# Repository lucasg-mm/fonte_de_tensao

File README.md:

# Projeto 1 da Disciplina SCC0180: Fonte de Tensão

## Autor
Lucas Gabriel Mendes Miranda, 10265892

## Objetivo
Projetar uma fonte de tensão que forneça, na saída, uma tensão entre 3V e 12V com capacidade de 100mA.

## Diagrama da Fonte

## Lista de Componentes Utilizados

| Nome do Componente | Valor | Preço |
| --- | --- | --- |
| [Transformador](https://www.soldafria.com.br/componentes-eletronicos/transformador/2a/transformador-15v-2a-entrada-110-220vac) | 15V 2A | R$39,82 |
| [Diodo Zener BZX55C](https://www.baudaeletronica.com.br/diodo-zener-bzx55c-13v-0-5w.html) | 13V 0,5W | R$ 0,09 |
| [Resistor](https://www.baudaeletronica.com.br/resistor-1k8-5-1-4w.html) | 1,8k 5% (1/4W) | R$ 0,08 |
| [Resistor](https://www.baudaeletronica.com.br/resistor-1k8-1-2w.html) | 1k 5% (1/2W) | R$ 0,14 |
| [Resistor](https://www.baudaeletronica.com.br/resistor-2k2-5-1-4w.html) | 2,2k 5% (1/4W) | R$ 0,08 |
| [Potenciômetro Linear](https://www.baudaeletronica.com.br/potenciometro-linear-de-5k-5000.html) | 5k (0,2W) | R$ 1,09 |
| [Capacitor Eletrolítico](https://www.baudaeletronica.com.br/capacitor-eletrolitico-470uf-25v.html) | 470 uF / 25V | R$ 0,33 |
| 4 [Diodos 1N5404](https://www.baudaeletronica.com.br/diodo-1n5404.html) (para a ponte) | 3A | R$ 0,36 (cada)|
| [LED difuso 5mm vermelho](https://www.baudaeletronica.com.br/led-difuso-5mm-vermelho.html) | 2V 20mA | R$ 0,24 |
| [Transistor NPN BC337](https://www.baudaeletronica.com.br/transistor-npn-bc337.html) | VCEO = 45V, IC = 500mA | R$ 0,17 |

## Partes do Circuito e Justificativa dos Componentes

### Fonte de Tensão AC de 127V
A fonte foi projetada para funcionar com o fornecimento de uma tensão de 127V (RMS) em corrente alternada (AC). O simulador usado (Falstad) permite apenas definir a tensão máxima (peak) de uma fonte AC. Mas, sabemos que:

Então a tensão máxima dessa fonte foi ajustada para 179.6V no simulador. 

### Transformador
O transformador tem como objetivo diminuir o valor da tensão de 127V. Para determinar o valor do transformador necessário, foi preciso realizar alguns cálculos:

* Sabemos que a nossa fonte precisa fornecer no máximo **12V**

* Cada diodo tem uma queda de **0.7V**

* O circuito regulador precisa de aproximadamente **8.46V** para funcionar (quando a fonte fornece *12V*)

Somando os valores em negrito, temos uma tensão de pico de aproximadamente 21.16V, por isso, precisamos de um transformador de, no mínimo, 15V RMS, capaz de fornecer 500 mA.

### Ponte de Diodos (Rectifier)
A ponte de diodos converte a tensão AC do transformador numa tensão DC pulsante. 

### Capacitor (Filtro)
O capacitor diminui os pulsos da tensão fornecida pela ponte de diodos. O capacitor está submetido a uma tensão de aproximadamente 20V, porém, foi listado na lista de materiais com 25V para evitar queimar o dispositivo (temos uma margem de segurança de 5V).

### LED
Apenas para indicar qua a fonte está ligada. Possui um resistor de 1k conectado em série para não queimar o diodo.

### Circuito Regulador
Esse circuito elimina o ripple da tensão fornecida pelo filtro, resultando na tensão DC entre 3V e 12V desejada (ela é definida manipulando o potenciômetro).

### Saída
Representamos o dispositivo a ser alimentado por um resistor de 120 ohms.

## Link para o Circuito no Falstad
http://tinyurl.com/ycgv9rr6

## Esquemático Feito no EAGLE
Corresponde ao arquivo `fonte.sch`

## PCB Feito no EAGLE
Corresponde ao arquivo `fonte.brd`

## Vídeo

https://www.youtube.com/watch?v=4Xhk5OuTBfk

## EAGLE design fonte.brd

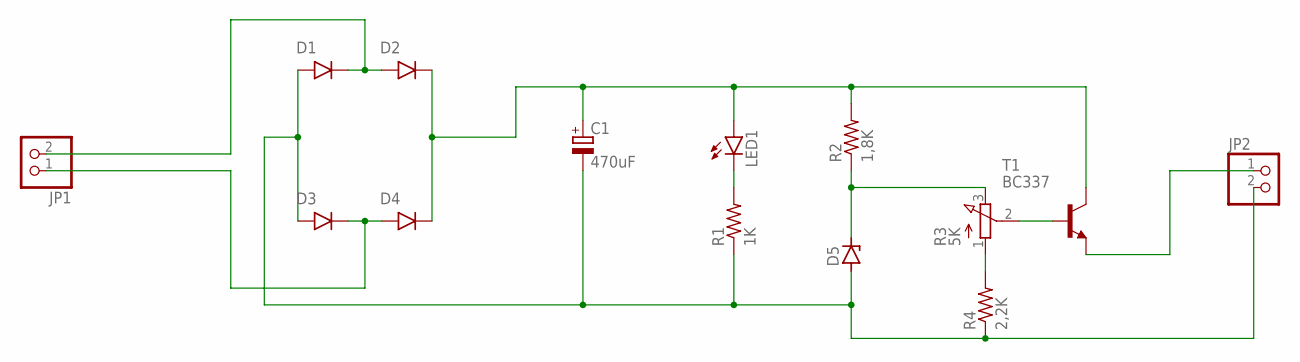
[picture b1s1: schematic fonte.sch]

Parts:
C1: 470uF; E3,5-10
D1, D2, D3, D4: 1N4001; DO41-10
D5: ZENER-DIODEDO34-7; DO34Z7
JP1, JP2: PINHD-1X2; 1X02
LED1: LED5MM
R1: 1K; 0309/12
R2: 1,8K; 0309/12
R3: 5K; 3RP/1610N
R4: 2,2K; 0309/12
T1: BC337; TO92

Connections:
unnamed: D1.C (CATHODE), D2.A (ANODE), JP1.2
unnamed: D3.C (CATHODE), D4.A (ANODE), JP1.1
unnamed: C1.-, D1.A (ANODE), D3.A (ANODE), D5.A, JP2.2, R1.1, R4.1
unnamed: C1.+, D2.C (CATHODE), D4.C (CATHODE), LED1.A, R2.2, T1.3 (C)
unnamed: D5.C, R2.1, R3.3 (E)
unnamed: R3.1 (A), R4.2
unnamed: LED1.K (C), R1.2
unnamed: R3.2 (S), T1.2 (B)
unnamed: JP2.1, T1.1 (E)

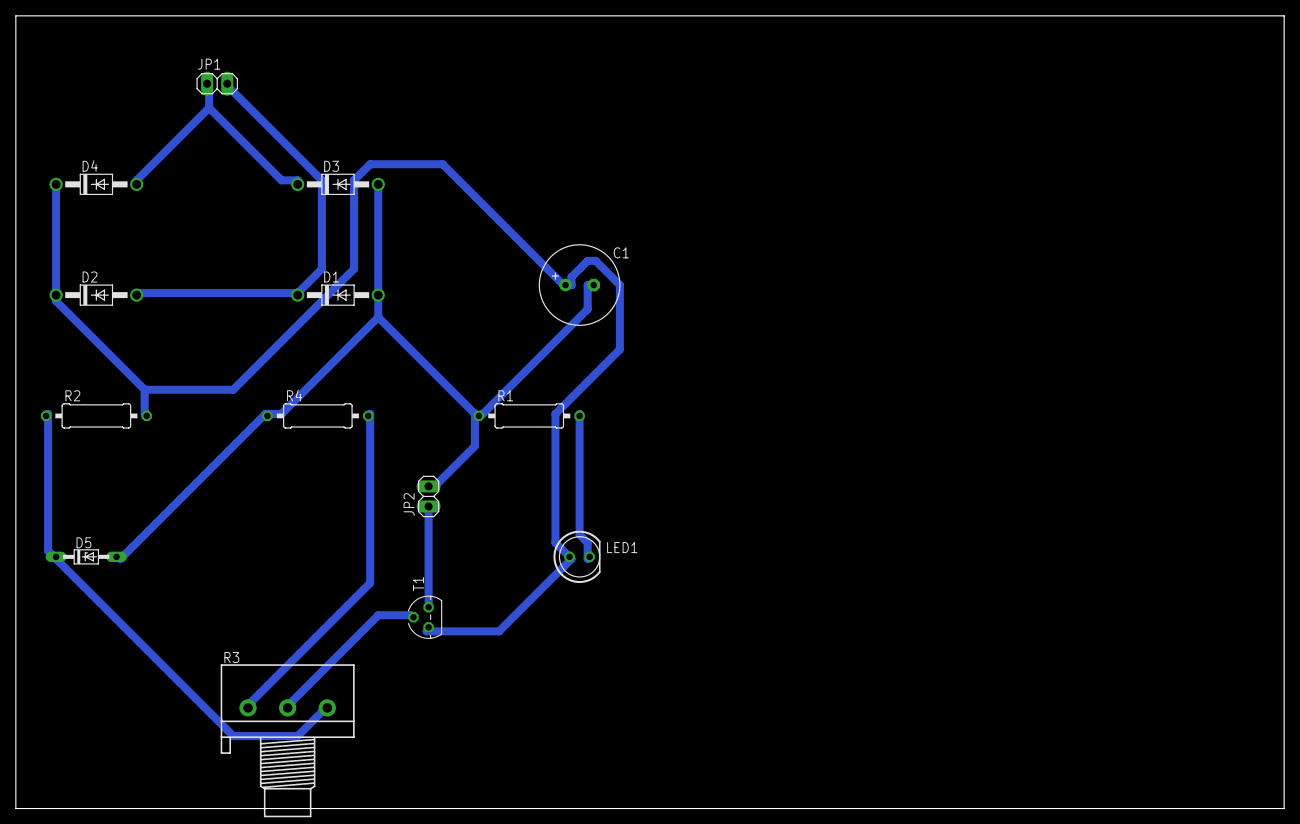
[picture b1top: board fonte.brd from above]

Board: 2 copper layers, 160.0 x 100.0 mm, 14 parts (0 on the bottom side), 9 nets.

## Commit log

2020-06-28 Adiciona foto do circuito, lista de componentes e link para a simulação no Falstad
2020-06-28 Adiciona simulação do Falstad em .txt
2020-06-29 Adiciona arquivos do projeto no EAGLE
